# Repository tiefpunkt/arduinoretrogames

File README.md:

# Arduino Retro Gameconsole
Rob Cai published two Instructables in which he used an Arduino to emulate some old-school videogames. I didn’t want to build the project on protoboard, so I designed these PCBs for that.

## Hardware

The hardware of the retro videogame console is made up of a mainboard,
and two different controller types.

### The Mainboard

The mainboard runs the video games, and connect to the VGA monitor, one
or two controllers, and to power. It's made up of an Arduino Pro Mini, a
few resistors, some more connectors, and possibly a buzzer for audio.

#### Parts

| Part Number | Type                                     |
|-------------|------------------------------------------|
| R1          | Resistor 470Ω                            |
| R2          | Resistor 470Ω                            |
| R3          | Resistor 68Ω                             |
| R4          | Resistor 68Ω                             |
| P1          | Jumper 2x3 for color setting (see below) |
| P2          | Jumper 2x3 for color setting (see below) |

#### Colors

The arduino outputs two color signals, and you can choose, which colors
those should represent on the monitor. To do that, you have the two
color jumpers in the bottom right corner of the board. You can check out
our recommendations in the table below.

| Game   | Color1 | Jumper Setting for Color 1 | Color 2 | Jumper Setting for Color 2 |
|--------|--------|----------------------------|---------|----------------------------|
| Tetris | ???    | : : \[:\]                  | ???     | : \[:\] :                  |

### The Controllers

Depending on the game you want to play, two different types of
controllers are necessary. One has one button and one knob
(potentiometer), the other one simply 4 buttons. Both are based on the
same PCB, just with different parts put in place

<table>
<thead>
<tr class="header">
<th><p>Part number</p></th>
<th><p>Description</p></th>
<th><p>Necessary for<br />
Button+Knob controller</p></th>
<th><p>Necessary for<br />
4 buttons controller</p></th>
</tr>
</thead>
<tbody>
<tr class="odd">
<td><p>D1</p></td>
<td><p>5mm LED</p></td>
<td><p>(x)</p></td>
<td><p>(x)</p></td>
</tr>
<tr class="even">
<td><p>J1</p></td>
<td><p>RJ12 connector</p></td>
<td><p>x</p></td>
<td><p>x</p></td>
</tr>
<tr class="odd">
<td><p>R1</p></td>
<td><p>Resistor 150Ω</p></td>
<td><p>(x)</p></td>
<td><p>(x)</p></td>
</tr>
<tr class="even">
<td><p>R2</p></td>
<td><p>Resistor 1kΩ</p></td>
<td><p>-</p></td>
<td><p>x</p></td>
</tr>
<tr class="odd">
<td><p>R3</p></td>
<td><p>Resistor 1kΩ</p></td>
<td><p>-</p></td>
<td><p>x</p></td>
</tr>
<tr class="even">
<td><p>R4</p></td>
<td><p>Resistor 1kΩ</p></td>
<td><p>-</p></td>
<td><p>x</p></td>
</tr>
<tr class="odd">
<td><p>R5</p></td>
<td><p>Resistor 1kΩ</p></td>
<td><p>x</p></td>
<td><p>x</p></td>
</tr>
<tr class="even">
<td><p>RV2</p></td>
<td><p>Potentiometer 10kΩ</p></td>
<td><p>x</p></td>
<td><p>-</p></td>
</tr>
<tr class="odd">
<td><p>RV4</p></td>
<td><p>Potentiometer 10kΩ</p></td>
<td><p>-</p></td>
<td><p>-</p></td>
</tr>
<tr class="even">
<td><p>SW1</p></td>
<td><p>Pushbutton</p></td>
<td><p>-</p></td>
<td><p>x</p></td>
</tr>
<tr class="odd">
<td><p>SW2</p></td>
<td><p>Pushbutton</p></td>
<td><p>-</p></td>
<td><p>x</p></td>
</tr>
<tr class="even">
<td><p>SW3</p></td>
<td><p>Pushbutton</p></td>
<td><p>-</p></td>
<td><p>x</p></td>
</tr>
<tr class="odd">
<td><p>SW4</p></td>
<td><p>Pushbutton</p></td>
<td><p>x</p></td>
<td><p>x</p></td>
</tr>
</tbody>
</table>

R1 and D1 are for an optional LED which lights up when the controller is
connected to the mainboard.

## Software

The games for the Arduino Retro Videogame Console are made by Rob Cai,
and can be found on Instructables

* [Pong, Breakout, Bomber, Etch-a-Sketch in one](http://www.instructables.com/id/Arduino-VGA-Games-4-in-1/)
* [Pong](http://www.instructables.com/id/VGA-Pong-with-Arduino-Uno/)

## Resources
* [Arduino Lib](https://github.com/smaffer/vgax)

## License
Licensed under Creative Commons Attribution-ShareAlike 4.0 Unported License (CC BY-SA 4.0)

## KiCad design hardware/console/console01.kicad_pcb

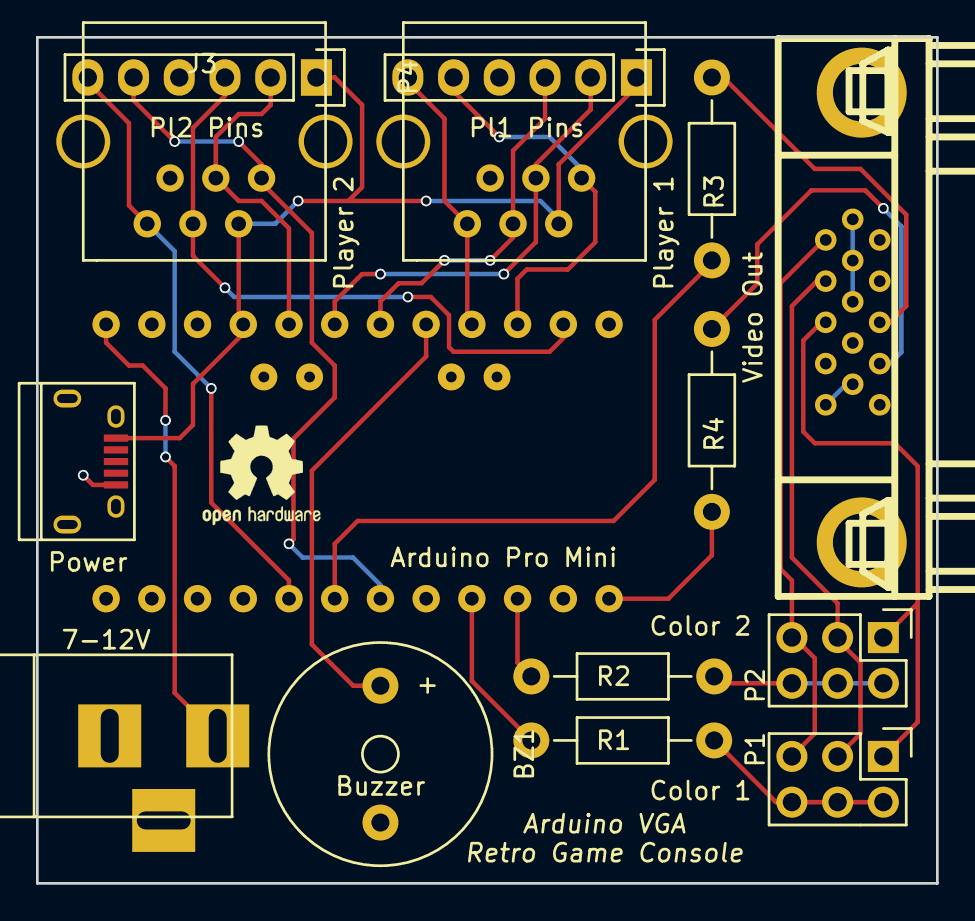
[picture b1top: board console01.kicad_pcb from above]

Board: 2 copper layers, 50.0 x 47.0 mm, 15 parts (0 on the bottom side), 23 nets.

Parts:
BZ1: Buzzer; Buzzer_12x9.5RM7.6
CON1: 7-12V; BARREL_JACK
J1: Video Out; DB_15F-VGA
J2: Player 1; RJ12_E
J3: Player 2; RJ12_E
P1: Color 1; Pin_Header_Straight_2x03
P2: Color 2; Pin_Header_Straight_2x03
P3: Power; USB_Micro-B
P4: Pl2 Pins; Pin_Header_Straight_1x06
P5: Pl1 Pins; Pin_Header_Straight_1x06
R1, R2: 470; Resistor_Horizontal_RM10mm
R3, R4: 68; Resistor_Horizontal_RM10mm
uP1: Arduino Pro Mini; ArduProMini-6

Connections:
GND: BZ1.2, CON1.2, J1.5, J1.6, J1.7, J1.8, J1.10, J2.5, J3.5, P3.5, P3.6, P4.4, P5.4, uP1.20
unnamed: BZ1.1, uP1.26
unnamed: CON1.1, uP1.19
unnamed: J1.1, P1.5, P2.5
unnamed: J1.2, P1.3, P2.3
unnamed: J1.3, P1.1, P2.1
unnamed: J1.13, R3.2
unnamed: J1.14, R4.2
unnamed: P1.2, P1.4, P1.6, R1.2
unnamed: P2.2, P2.4, P2.6, R2.2
unnamed: R1.1, uP1.15
unnamed: R2.1, uP1.16
unnamed: R3.1, uP1.12
unnamed: R4.1, uP1.18
P1.1: J2.3, P5.2, uP1.24
P1.2: J2.4, P5.3, uP1.25
P1.3: J2.1, P5.5, uP1.28
P1.4: J2.6, P5.6, uP1.27
P2.1: J3.3, P4.2, uP1.23
P2.2: J3.4, P4.3, uP1.29
P2.3: J3.1, P4.5, uP1.13
P2.4: J3.6, P4.6, uP1.11
VCC: J2.2, J3.2, P3.1, P4.1, P5.1, uP1.22

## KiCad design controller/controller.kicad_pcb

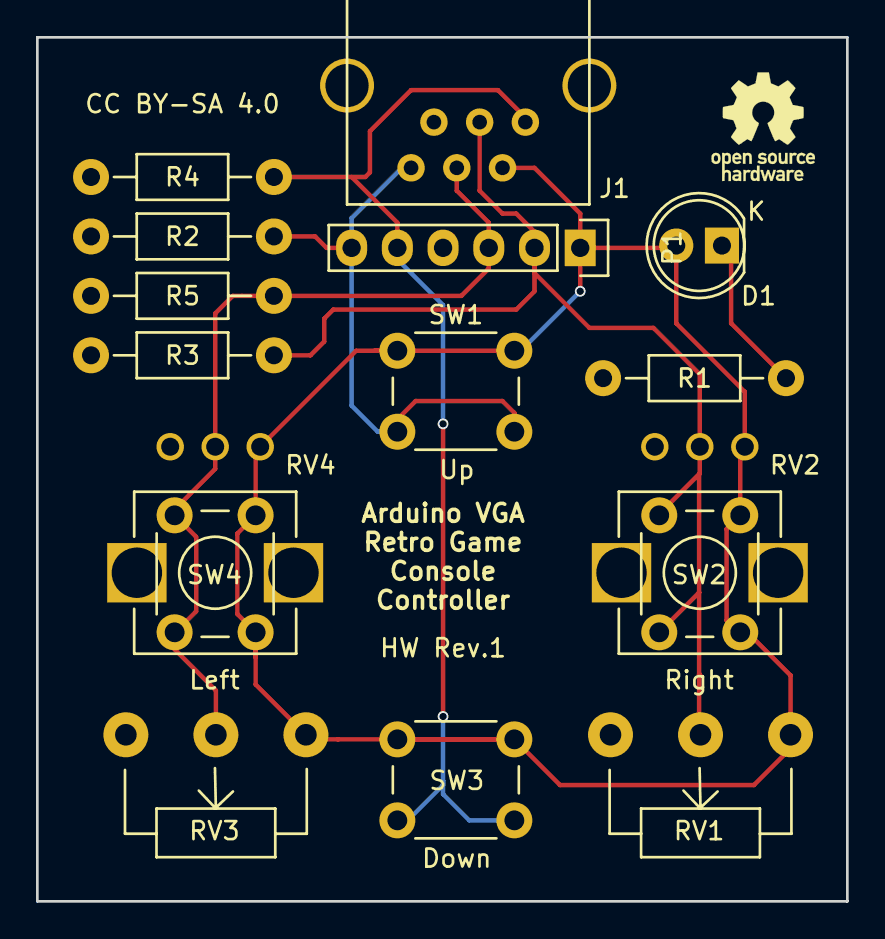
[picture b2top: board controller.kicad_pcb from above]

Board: 2 copper layers, 45.0 x 48.0 mm, 16 parts (0 on the bottom side), 7 nets.

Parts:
D1: LED; LED-5MM
J1: RJ12; RJ12_E
P1: CONN_01X06; Pin_Header_Straight_1x06
R1, R2, R3, R4, R5: 1k; Resistor_Horizontal_RM10mm
RV1, RV3: 10k; Potentiometer_WirePads
RV2, RV4: 10k; Potentiometer_Alpha-RV09
SW1: Up; SW_PUSH_6mm_h5mm
SW2: Right; SW_PUSH_6mm_h5mm
SW3: Down; SW_PUSH_6mm_h5mm
SW4: Left; SW_PUSH_6mm_h5mm

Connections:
GND: J1.5, P1.4, R1.2, R2.2, R3.2, R4.2, R5.2, RV1.3, RV2.3, RV3.3, RV4.3
unnamed: D1.1, R1.1
VCC: D1.2, J1.2, P1.1, RV1.1, RV2.1, RV3.1, RV4.1, SW1.1, SW2.1, SW3.1, SW4.1
in1: J1.3, P1.2, R3.1, RV1.2, RV2.2, SW2.2
in2: J1.4, P1.3, R5.1, RV3.2, RV4.2, SW4.2
in3: J1.1, P1.5, R4.1, SW3.2
in4: J1.6, P1.6, R2.1, SW1.2

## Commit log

2017-03-13 inital commit
2017-04-17 final version for PCB production
2017-04-17 folders, add games
2021-03-04 README
2021-03-04 README copy/paste corrections
